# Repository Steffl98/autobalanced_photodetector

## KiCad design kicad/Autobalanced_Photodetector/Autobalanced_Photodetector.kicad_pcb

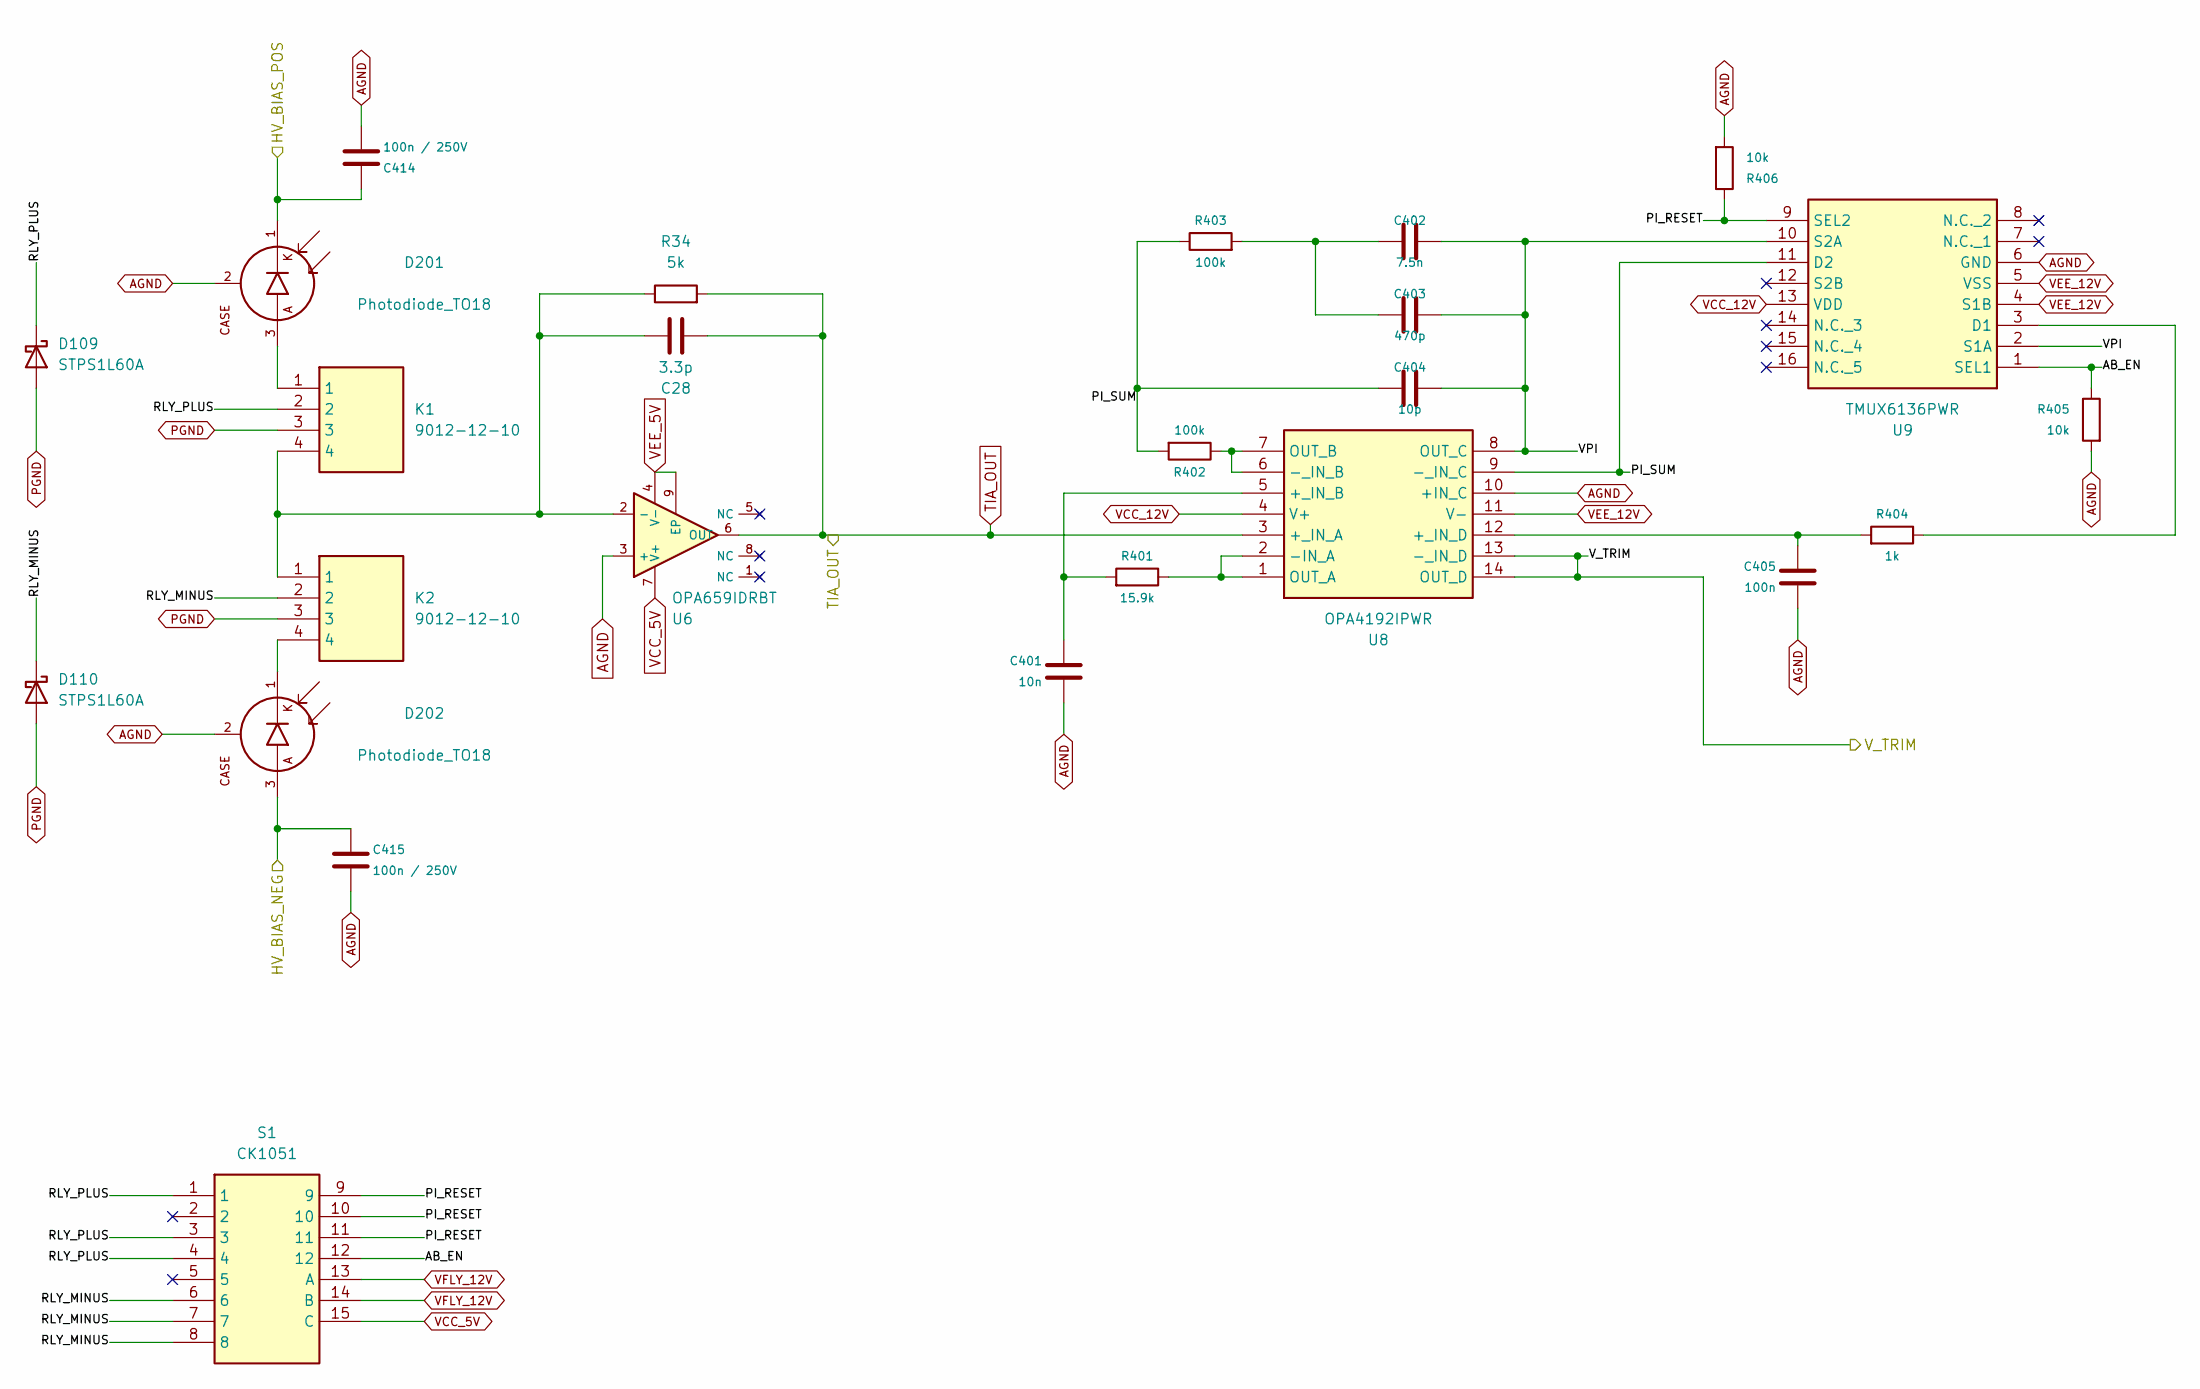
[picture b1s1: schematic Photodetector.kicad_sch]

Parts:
C28: 3.3p
C401: 10n; C_0603_1608Metric
C402: 7.5n; C_0603_1608Metric
C403: 470p; C_0603_1608Metric
C404: 10p; C_0603_1608Metric
C405: 100n; C_0603_1608Metric
C414, C415: 100n / 250V
D109, D110: STPS1L60A; D_SMA; MPN STPS1L60A
D201, D202: Photodiode_TO18; TO-18-3_Window
K1, K2: 9012-12-10; 90121210; Mouser Part Number 816-9012-12-10
R34: 5k
R401: 15.9k; R_0603_1608Metric
R402, R403: 100k; R_0603_1608Metric
R404: 1k; R_0603_1608Metric
R405, R406: 10k; R_0603_1608Metric
S1: CK1051; Manufacturer_Part_Number CK1051; Mouser Part Number 105-CK1051
U6: OPA659IDRBT; OPA659_DRB; MPN OPA659IDRBT; Mouser Part Number 595-OPA659IDRBT
U8: OPA4192IPWR; SOP65P640X120-14N; Manufacturer_Part_Number OPA4192IPWR; Mouser Part Number 595-OPA4192IPWR
U9: TMUX6136PWR; SOP65P640X120-16N; Manufacturer_Part_Number TMUX6136PWR; Mouser Part Number 595-TMUX6136PWR

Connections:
/HV_Regulator_Neg/HV_BIAS_NEG: C415.1, D202.3 (A); also elsewhere on the board
/HV_Regulator_Pos/HV_BIAS_POS: C414.1, D201.1 (K); also elsewhere on the board
/Photodetector/AB_EN: R405.1, S1.12, U9.1 (SEL1)
/Photodetector/PI_RESET: R406.1, S1.9, S1.10, S1.11, U9.9 (SEL2)
/Photodetector/PI_SUM: C404.1, R402.2, R403.1, U8.9 (-_IN_C), U9.11 (D2)
/Photodetector/RLY_MINUS: D110.1 (K), K2.2, S1.6, S1.7, S1.8
/Photodetector/RLY_PLUS: D109.1 (K), K1.2, S1.1, S1.3, S1.4
/Photodetector/VPI: C402.2, C403.2, C404.2, U8.8 (OUT_C), U9.2 (S1A), U9.10 (S2A)
/Photodetector/V_TRIM: U8.13 (-_IN_D), U8.14 (OUT_D); also elsewhere on the board
unnamed: C402.1, C403.1, R403.2
unnamed: D201.3 (A), K1.1
unnamed: D202.1 (K), K2.4
unnamed: C28.1, K1.4, K2.1, R34.1, U6.2 (-)
unnamed: C401.1, R401.2, U8.5 (+_IN_B)
unnamed: C405.1, R404.2, U8.12 (+_IN_D)
unnamed: R401.1, U8.1 (OUT_A), U8.2 (-IN_A)
unnamed: R402.1, U8.6 (-_IN_B), U8.7 (OUT_B)
unnamed: R404.1, U9.3 (D1)
PGND: D109.2 (A), D110.2 (A), K1.3, K2.3; also elsewhere on the board
TIA_OUT: C28.2, R34.2, U6.6 (OUT), U8.3 (+_IN_A)
VCC_5V: S1.15 (C), U6.7 (V+); also elsewhere on the board
VCC_12V: U8.4 (V+), U9.13 (VDD); also elsewhere on the board
VEE_5V: U6.4 (V-), U6.9 (EP); also elsewhere on the board
VEE_12V: U8.11 (V-), U9.4 (S1B), U9.5 (VSS); also elsewhere on the board
VFLY_12V: S1.13 (A), S1.14 (B); also elsewhere on the board

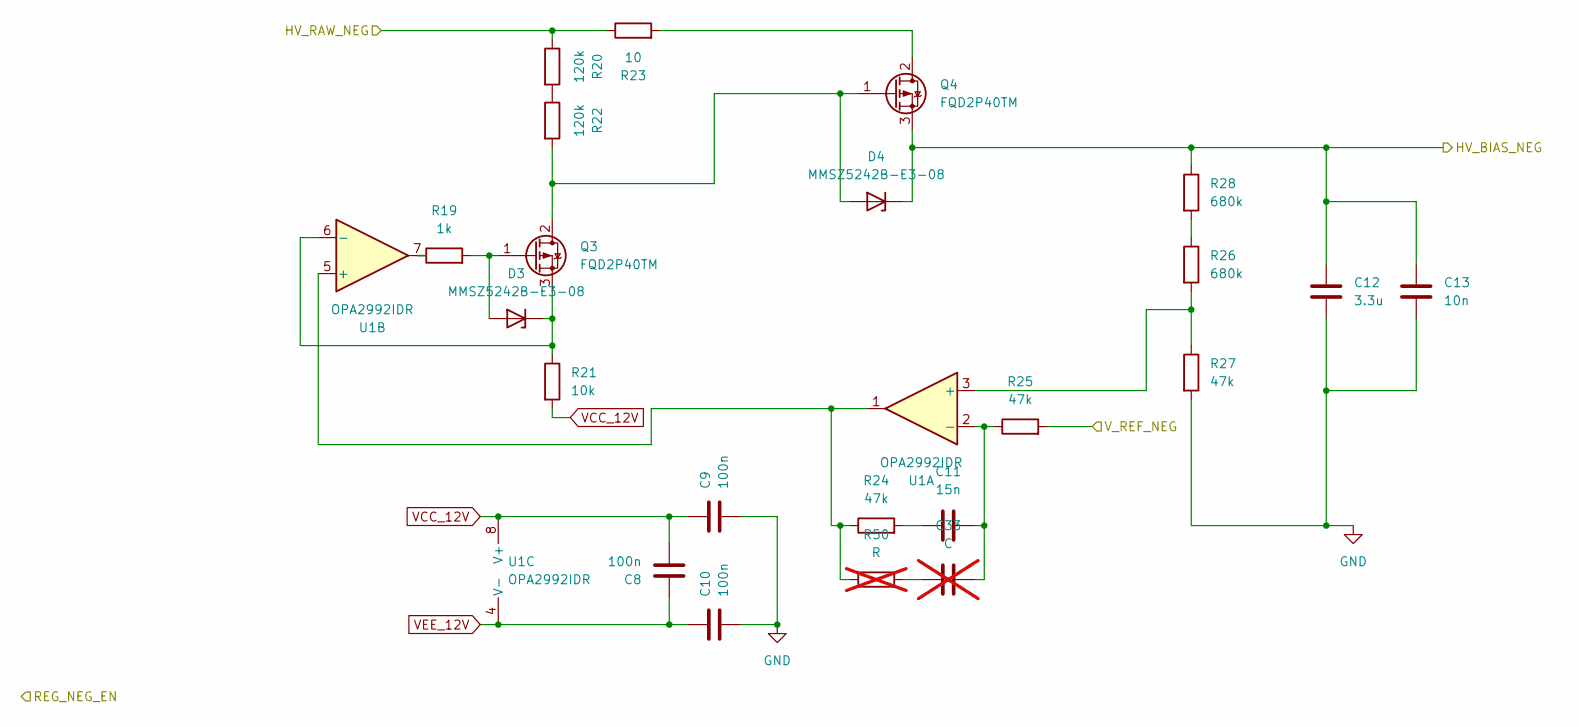
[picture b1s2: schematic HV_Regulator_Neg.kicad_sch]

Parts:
C8, C9, C10: 100n; C_0805_2012Metric; MPN C0805Y104K1RACTU
C11: 15n; C_0805_2012Metric; MPN C0805X103J5GACTU
C12: 3.3u; C_Rect_L29.0mm_W12.2mm_P27.50mm_MKT; MPN C4AQJBU4330M1WJ
C13: 10n; C_1206_3216Metric; MPN C1206C103JBGACAUTO7210
C33: C; C_0805_2012Metric; not fitted
D3, D4: MMSZ5242B-E3-08; D_SOD-123
Q3, Q4: FQD2P40TM; TO-252-2
R19: 1k; R_0805_2012Metric
R20, R22: 120k; R_1206_3216Metric
R21: 10k; R_0805_2012Metric
R23: 10; R_0805_2012Metric
R24, R25, R27: 47k; R_0805_2012Metric
R26, R28: 680k; R_1206_3216Metric
R50: R; R_0805_2012Metric; not fitted
U1: OPA2992IDR; SOIC-8_3.9x4.9mm_P1.27mm

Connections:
/Flyback/HV_RAW_NEG: R20.1, R23.1; also elsewhere on the board
/HV_Regulator_Neg/HV_BIAS_NEG: C12.1, C13.1, D4.1 (K), Q4.3 (S), R28.1; also elsewhere on the board
/HV_Regulator_Neg/V_REF_NEG: R25.2; also elsewhere on the board
unnamed: C11.1, R24.2
unnamed: C33.1, R50.2
unnamed: D3.2 (A), Q3.1 (G), R19.2
unnamed: D3.1 (K), Q3.3 (S), R21.1, U1.6 (-)
unnamed: D4.2 (A), Q3.2 (D), Q4.1 (G), R22.2
unnamed: Q4.2 (D), R23.2
unnamed: R19.1, U1.7
unnamed: R20.2, R22.1
unnamed: R26.1, R28.2
unnamed: R26.2, R27.1, U1.3 (+)
unnamed: C11.2, C33.2, R25.1, U1.2 (-)
unnamed: R24.1, R50.1, U1.1, U1.5 (+)
VCC_12V: C8.2, C9.1, R21.2, U1.8 (V+); also elsewhere on the board
VEE_12V: C8.1, C10.1, U1.4 (V-); also elsewhere on the board

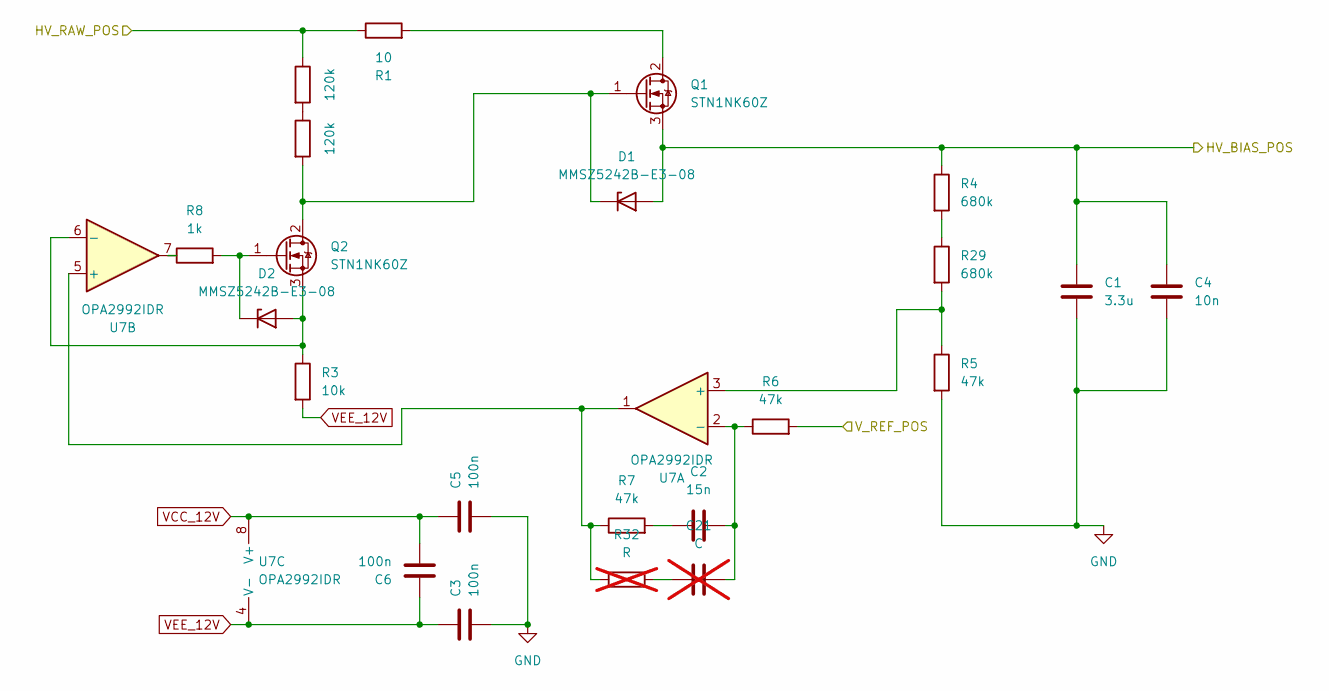
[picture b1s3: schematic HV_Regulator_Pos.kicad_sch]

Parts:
C1: 3.3u; C_Rect_L29.0mm_W12.2mm_P27.50mm_MKT; MPN C4AQJBU4330M1WJ
C2: 15n; C_0805_2012Metric; MPN C0805X103J5GACTU
C3, C5, C6: 100n; C_0805_2012Metric; MPN C0805Y104K1RACTU
C4: 10n; C_1206_3216Metric; MPN C1206C103JBGACAUTO7210
C21: C; C_0805_2012Metric; not fitted
D1, D2: MMSZ5242B-E3-08; D_SOD-123
Q1, Q2: STN1NK60Z; SOT-223
R1: 10; R_0805_2012Metric
R2, R9: 120k; R_1206_3216Metric
R3: 10k; R_0805_2012Metric
R4, R29: 680k; R_1206_3216Metric
R5, R6, R7: 47k; R_0805_2012Metric
R8: 1k; R_0805_2012Metric
R32: R; R_0805_2012Metric; not fitted
U7: OPA2992IDR; SOIC-8_3.9x4.9mm_P1.27mm

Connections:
/Flyback/HV_RAW_POS: R1.1, R9.1; also elsewhere on the board
/HV_Regulator_Pos/HV_BIAS_POS: C1.1, C4.1, D1.2 (A), Q1.3 (S), R4.1; also elsewhere on the board
/HV_Regulator_Pos/V_REF_POS: R6.2; also elsewhere on the board
unnamed: C2.1, R7.2
unnamed: C21.1, R32.2
unnamed: D1.1 (K), Q1.1 (G), Q2.2 (D), R2.2
unnamed: D2.2 (A), Q2.3 (S), R3.1, U7.6 (-)
unnamed: D2.1 (K), Q2.1 (G), R8.2
unnamed: Q1.2 (D), R1.2
unnamed: R2.1, R9.2
unnamed: R8.1, U7.7
unnamed: R4.2, R29.1
unnamed: R5.1, R29.2, U7.3 (+)
unnamed: C2.2, C21.2, R6.1, U7.2 (-)
unnamed: R7.1, R32.1, U7.1, U7.5 (+)
VCC_12V: C5.1, C6.2, U7.8 (V+); also elsewhere on the board
VEE_12V: C3.1, C6.1, R3.2, U7.4 (V-); also elsewhere on the board

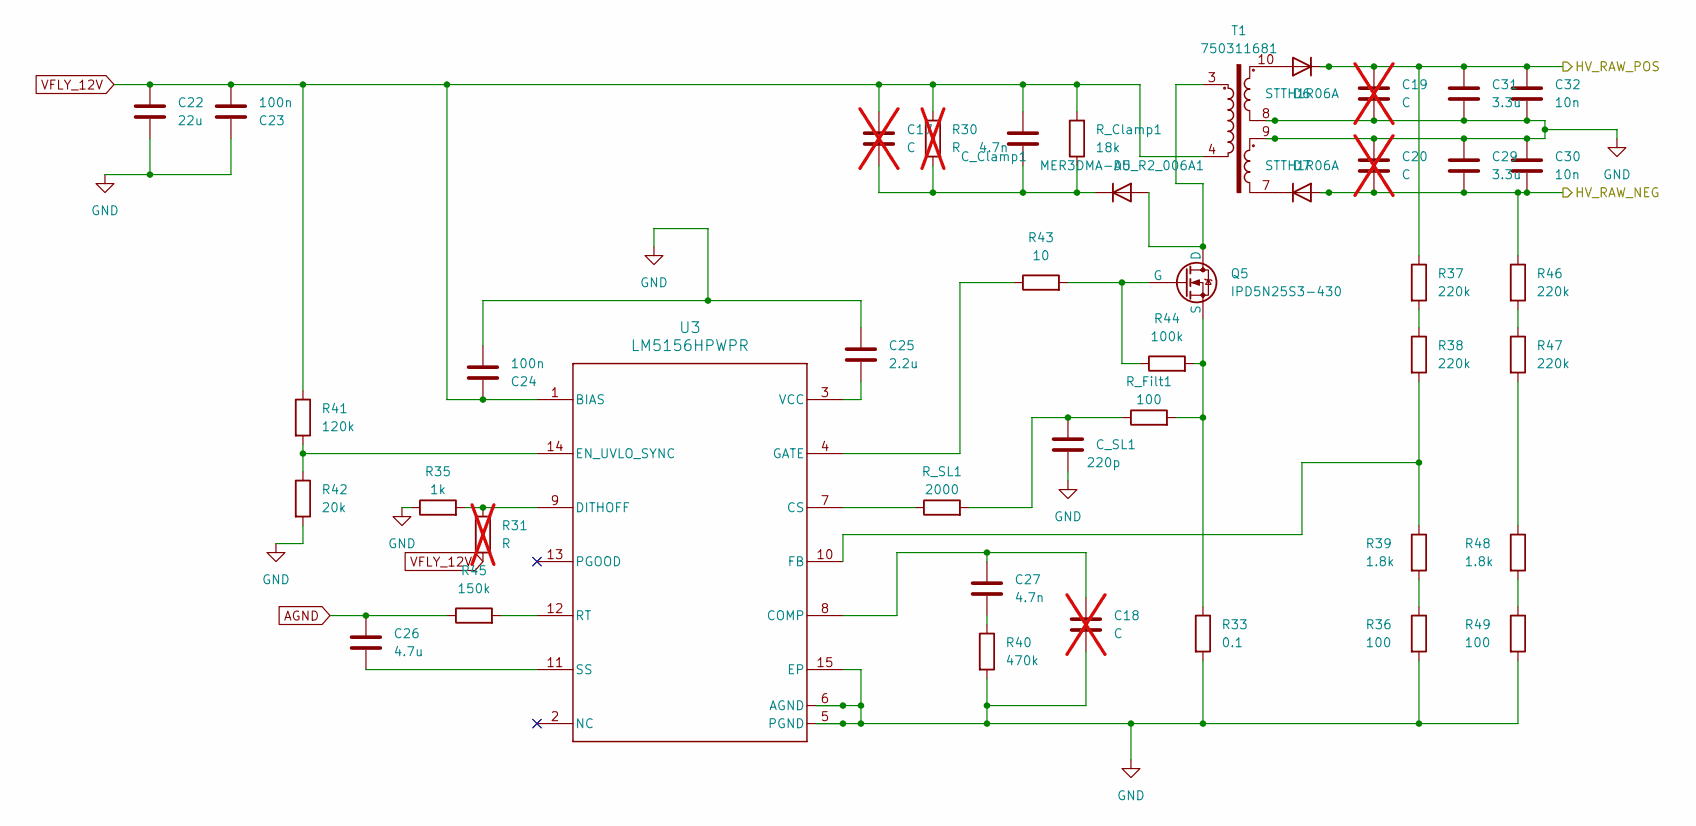
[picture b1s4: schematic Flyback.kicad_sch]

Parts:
C17, C18, C19, C20: C; C_0805_2012Metric; not fitted
C22: 22u; C_1210_3225Metric; MPN C3225X7R1E226M250AB
C23, C24: 100n; C_0805_2012Metric; MPN C0805Y104K1RACTU
C25: 2.2u; C_0805_2012Metric; MPN GRM21BR71C225KA12L
C26: 4.7u; C_0805_2012Metric; MPN CL21A475KAQNNNG
C27: 4.7n; C_0805_2012Metric; MPN GRM2165C1H472JA01D
C29, C31: 3.3u; C_Rect_L29.0mm_W12.2mm_P27.50mm_MKT; MPN C4AQJBU4330M1WJ
C30, C32: 10n; C_1206_3216Metric; MPN C1206C103JBGACAUTO7210
C_Clamp1: 4.7n; C_1206_3216Metric; MPN C1206C472JBGACTU
C_SL1: 220p; C_0805_2012Metric; MPN C0G
D5: MER3DMA-AU_R2_006A1; D_SMA
D6, D7: STTH1R06A; D_SMA
Q5: IPD5N25S3-430; TO-252-2
R30, R31: R; R_0805_2012Metric; not fitted
R33: 0.1; R_0805_2012Metric
R35: 1k; R_0805_2012Metric
R36, R49: 100; R_0805_2012Metric
R37, R38, R46, R47: 220k; R_1206_3216Metric
R39, R48: 1.8k; R_0805_2012Metric
R40: 470k; R_0805_2012Metric
R41: 120k; R_0805_2012Metric
R42: 20k; R_0805_2012Metric
R43: 10; R_0805_2012Metric
R44: 100k; R_0805_2012Metric
R45: 150k; R_0805_2012Metric
R_Clamp1: 18k; R_0805_2012Metric
R_Filt1: 100; R_0805_2012Metric
R_SL1: 2000; R_0805_2012Metric
T1: 750311681; Wuerth_750311681
U3: LM5156HPWPR; PWP0014H-IPC_A

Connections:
/Flyback/HV_RAW_NEG: C20.2, C29.2, C30.2, D7.2 (A), R46.1; also elsewhere on the board
/Flyback/HV_RAW_POS: C19.1, C31.1, C32.1, D6.1 (K), R37.1; also elsewhere on the board
unnamed: C27.1, R40.1
unnamed: C_SL1.2, R_Filt1.1, R_SL1.2
unnamed 37: D5.2 (A), Q5.1 (D), T1.3; also elsewhere on the board
unnamed: C17.2, C_Clamp1.2, D5.1 (K), R30.2, R_Clamp1.1
unnamed 39: D6.2 (A), T1.10; also elsewhere on the board
unnamed 40: D7.1 (K), T1.7; also elsewhere on the board
unnamed: Q5.2 (G), R43.2, R44.1
unnamed: Q5.3 (S), R33.1, R44.2, R_Filt1.2
unnamed: R36.1, R39.2
unnamed: R37.2, R38.1
unnamed: R46.2, R47.1
unnamed: R47.2, R48.1
unnamed: R48.2, R49.1
unnamed: C18.1, C27.2, U3.8 (COMP)
unnamed: R_SL1.1, U3.7 (CS)
unnamed: R31.1, R35.2, U3.9 (DITHOFF)
unnamed: R41.2, R42.1, U3.14 (EN_UVLO_SYNC)
unnamed: R38.2, R39.1, U3.10 (FB)
unnamed: R43.1, U3.4 (GATE)
unnamed: R45.2, U3.12 (RT)
unnamed: C26.2, U3.11 (SS)
unnamed: C25.2, U3.3 (VCC)
VFLY_12V: C17.1, C22.1, C23.2, C24.1, C_Clamp1.1, R30.1, R31.2, R41.1, R_Clamp1.2, T1.4, U3.1 (BIAS); also elsewhere on the board

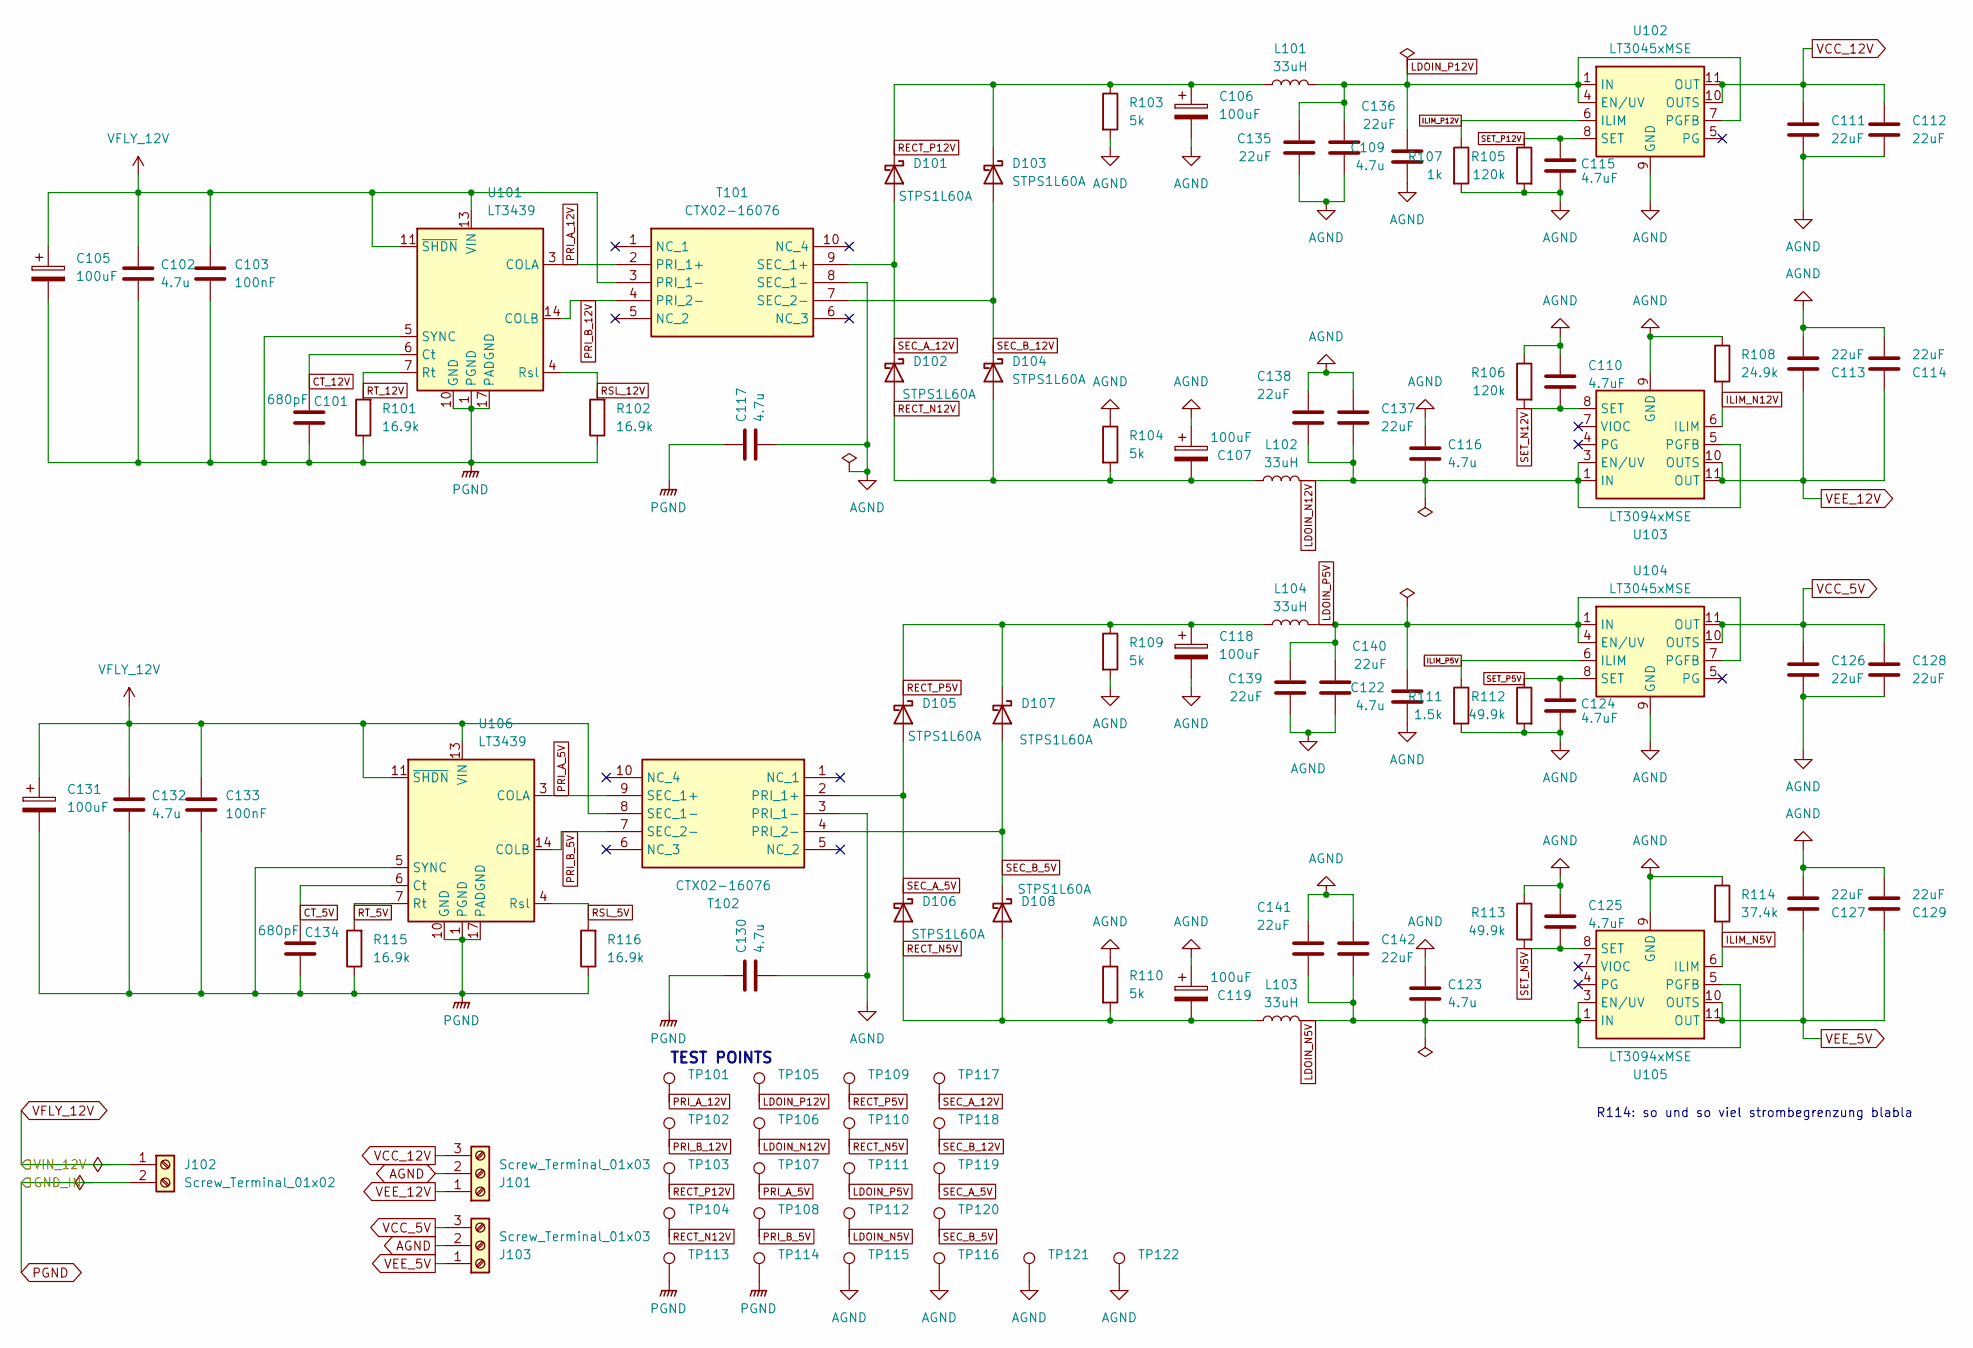
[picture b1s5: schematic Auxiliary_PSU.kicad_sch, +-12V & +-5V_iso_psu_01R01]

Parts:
C101, C134: 680pF; C_0603_1608Metric; MPN CC0603FRNPO9BN681
C102, C109, C116, C117, C122, C123, C130, C132: 4.7u; C_1206_3216Metric; MPN KGM31AR71E475KU
C103, C133: 100nF; C_0603_1608Metric; MPN CGA3E2X7R1E104M080AA
C105, C106, C107, C118, C119, C131: 100uF; CP_Elec_6.3x7.7; MPN GYE1V101MCQ1GS
C110, C115, C124, C125: 4.7uF; C_0603_1608Metric; MPN C1608X5R1E475K080AC
C111, C112, C113, C114, C126, C127, C128, C129, C135, C136, C137, C138, C139, C140, C141, C142: 22uF; C_1210_3225Metric; MPN MAAST32MSB7226MPNA01
D101, D102, D103, D104, D105, D106, D107, D108: STPS1L60A; D_SMA; MPN STPS1L60A
J101, J103: Screw_Terminal_01x03; TerminalBlock_Phoenix_MKDS-1,5-3-5.08_1x03_P5.08mm_Horizont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; MPN 1715734
J102: Screw_Terminal_01x02; TerminalBlock_Phoenix_MKDS-1,5-2-5.08_1x02_P5.08mm_Horizont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; MPN 1715721
L101, L102, L103, L104: 33uH; L_TDK_VLS5030EX
R101, R102, R115, R116: 16.9k; R_0603_1608Metric; MPN CPF0603F16K9C1
R103, R104, R109, R110: 5k; R_1206_3216Metric; MPN RT0603BRE075KL
R105, R106: 120k; R_0603_1608Metric; MPN RT0603BRD07120KL
R107: 1k; R_0603_1608Metric; MPN RT0603BRD071KL
R108: 24.9k; R_0603_1608Metric; MPN RT0603BRD0724K9L
R111: 1.5k; R_0603_1608Metric; MPN RT0603BRD071K5L
R112, R113: 49.9k; R_0603_1608Metric; MPN RT0603BRD0749K9L
R114: 37.4k; R_0603_1608Metric; MPN RT0603BRE0737K4L
T101, T102: CTX02-16076; CTX0216076; Mouser Part Number 704-CTX02-16076
TP101: PRI_A_12V; TestPoint_Pad_D1.5mm
TP102: PRI_B_12V; TestPoint_Pad_D1.5mm
TP103: RECT_P12V; TestPoint_Pad_D1.5mm
TP104: RECT_N12V; TestPoint_Pad_D1.5mm
TP105: LDOIN_P12V; TestPoint_Pad_D1.5mm
TP106: LDOIN_N12V; TestPoint_Pad_D1.5mm
TP107: PRI_A_5V; TestPoint_Pad_D1.5mm
TP108: PRI_B_5V; TestPoint_Pad_D1.5mm
TP109: RECT_P5V; TestPoint_Pad_D1.5mm
TP110: RECT_N5V; TestPoint_Pad_D1.5mm
TP111: LDOIN_P5V; TestPoint_Pad_D1.5mm
TP112: LDOIN_N5V; TestPoint_Pad_D1.5mm
TP113, TP114: PGND; TestPoint_Keystone_5000-5004_Miniature; MPN 5001
TP115, TP116, TP121, TP122: AGND; TestPoint_Keystone_5000-5004_Miniature; MPN 5001
TP117: SEC_A_12V; TestPoint_Pad_D1.5mm
TP118: SEC_B_12V; TestPoint_Pad_D1.5mm
TP119: SEC_A_5V; TestPoint_Pad_D1.5mm
TP120: SEC_B_5V; TestPoint_Pad_D1.5mm
U101, U106: LT3439; TSSOP-16-1EP_4.4x5mm_P0.65mm
U102, U104: LT3045xMSE; MSOP-12-1EP_3x4.039mm_P0.65mm_EP1.651x2.845mm; MPN LT3045HMSE#TRPBF
U103, U105: LT3094xMSE; MSOP-12-1EP_3x4.039mm_P0.65mm_EP1.651x2.845mm; MPN LT3094EMSE#TRPBF

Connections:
CT_5V: C134.1, U106.6 (Ct)
CT_12V: C101.1, U101.6 (Ct)
ILIM_N5V: R114.2, U105.6 (ILIM)
ILIM_N12V: R108.2, U103.6 (ILIM)
ILIM_P5V: R111.1, U104.6 (ILIM)
ILIM_P12V: R107.1, U102.6 (ILIM)
LDOIN_N5V: C123.2, C141.2, C142.2, L103.2, TP112.1, U105.1 (IN), U105.2 (IN), U105.3 (EN/UV), U105.5 (PGFB), U105.13 (IN)
LDOIN_N12V: C116.2, C137.2, C138.2, L102.2, TP106.1, U103.1 (IN), U103.2 (IN), U103.3 (EN/UV), U103.5 (PGFB), U103.13 (IN)
LDOIN_P5V: C122.1, C139.1, C140.1, L104.2, TP111.1, U104.1 (IN), U104.2 (IN), U104.3 (IN), U104.4 (EN/UV), U104.7 (PGFB)
LDOIN_P12V: C109.1, C135.1, C136.1, L101.2, TP105.1, U102.1 (IN), U102.2 (IN), U102.3 (IN), U102.4 (EN/UV), U102.7 (PGFB)
PGND: C101.2, C102.2, C103.2, C105.2, C117.1, C130.1, C131.2, C132.2, C133.2, C134.2, J102.2, R101.1, R102.1, R115.1, R116.1, TP113.1, TP114.1, U101.1 (PGND), U101.5 (SYNC), U101.10 (GND), U101.16 (PGND), U101.17 (PADGND), U106.1 (PGND), U106.5 (SYNC), U106.10 (GND), U106.16 (PGND), U106.17 (PADGND); also elsewhere on the board
PRI_A_5V: T102.9 (SEC_1+), TP107.1, U106.3 (COLA)
PRI_A_12V: T101.2 (PRI_1+), TP101.1, U101.3 (COLA)
PRI_B_5V: T102.7 (SEC_2-), TP108.1, U106.14 (COLB)
PRI_B_12V: T101.4 (PRI_2-), TP102.1, U101.14 (COLB)
RECT_N5V: C119.2, D106.2 (A), D108.2 (A), L103.1, R110.2, TP110.1
RECT_N12V: C107.2, D102.2 (A), D104.2 (A), L102.1, R104.2, TP104.1
RECT_P5V: C118.1, D105.1 (K), D107.1 (K), L104.1, R109.1, TP109.1
RECT_P12V: C106.1, D101.1 (K), D103.1 (K), L101.1, R103.1, TP103.1
RSL_5V: R116.2, U106.4 (Rsl)
RSL_12V: R102.2, U101.4 (Rsl)
RT_5V: R115.2, U106.7 (Rt)
RT_12V: R101.2, U101.7 (Rt)
SEC_A_5V: D105.2 (A), D106.1 (K), T102.2 (PRI_1+), TP119.1
SEC_A_12V: D101.2 (A), D102.1 (K), T101.9 (SEC_1+), TP117.1
SEC_B_5V: D107.2 (A), D108.1 (K), T102.4 (PRI_2-), TP120.1
SEC_B_12V: D103.2 (A), D104.1 (K), T101.7 (SEC_2-), TP118.1
SET_N5V: C125.2, R113.2, U105.8 (SET)
SET_N12V: C110.2, R106.2, U103.8 (SET)
SET_P5V: C124.1, R112.1, U104.8 (SET)
SET_P12V: C115.1, R105.1, U102.8 (SET)
VCC_5V: C126.1, C128.1, J103.3, U104.10 (OUTS), U104.11 (OUT), U104.12 (OUT); also elsewhere on the board
VCC_12V: C111.1, C112.1, J101.3, U102.10 (OUTS), U102.11 (OUT), U102.12 (OUT); also elsewhere on the board
VEE_5V: C127.1, C129.1, J103.1, U105.10 (OUTS), U105.11 (OUT), U105.12 (OUT); also elsewhere on the board
VEE_12V: C113.1, C114.1, J101.1, U103.10 (OUTS), U103.11 (OUT), U103.12 (OUT); also elsewhere on the board
VFLY_12V: C102.1, C103.1, C105.1, C131.1, C132.1, C133.1, J102.1, T101.3 (PRI_1-), T102.8 (SEC_1-), U101.11 (~SHDN), U101.13 (VIN), U106.11 (~SHDN), U106.13 (VIN); also elsewhere on the board

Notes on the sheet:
R114: so und so viel strombegrenzung blabla
TEST POINTS

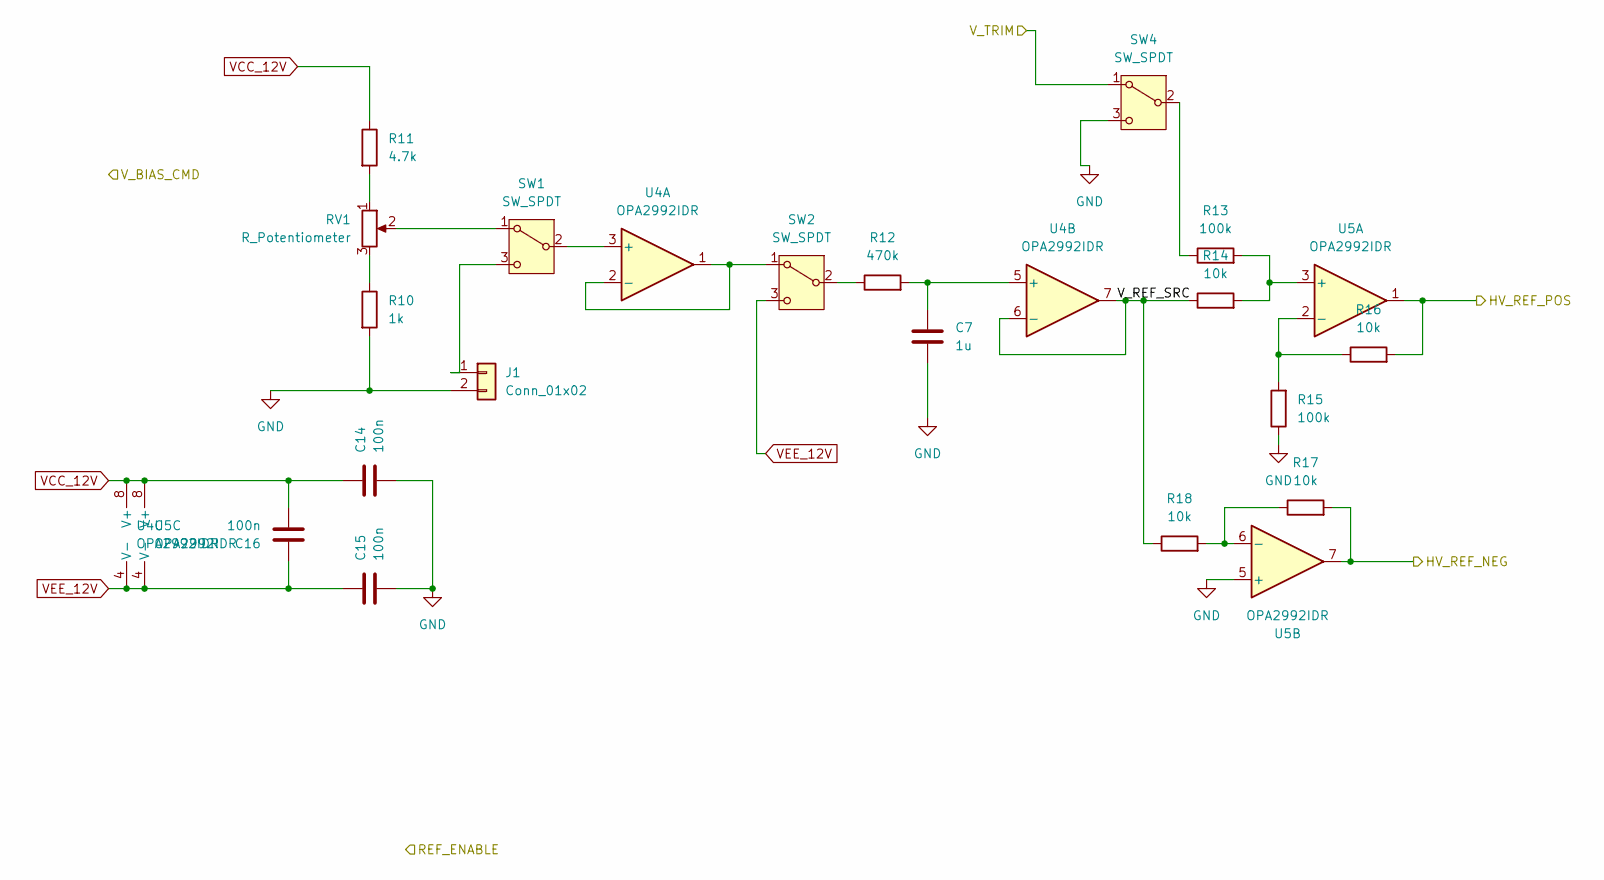
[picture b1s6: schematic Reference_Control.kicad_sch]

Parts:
C7: 1u; C_Rect_L13.0mm_W4.0mm_P10.00mm_FKS3_FKP3_MKS4; MPN MKS4C041003C00KSSD
C14, C15, C16: 100n; C_0805_2012Metric; MPN C0805Y104K1RACTU
J1: Conn_01x02; TerminalBlock_Phoenix_MKDS-1,5-2-5.08_1x02_P5.08mm_Horizont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; MPN 1715721
R10: 1k; R_0805_2012Metric
R11: 4.7k; R_0805_2012Metric
R12: 470k; R_0805_2012Metric
R13, R15: 100k; R_0805_2012Metric
R14, R16, R17, R18: 10k; R_0805_2012Metric
RV1: R_Potentiometer; Potentiometer_Bourns_PTV09A-1_Single_Vertical
SW1, SW2, SW4: SW_SPDT; SW_Slide_SPDT_Straight_CK_OS102011MS2Q; MPN OS102011MS2QN1
U4, U5: OPA2992IDR; SOIC-8_3.9x4.9mm_P1.27mm

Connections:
/HV_Regulator_Neg/V_REF_NEG: R17.2, U5.7; also elsewhere on the board
/HV_Regulator_Pos/V_REF_POS: R16.2, U5.1; also elsewhere on the board
/Photodetector/V_TRIM: SW4.1 (A); also elsewhere on the board
/Reference_Control/V_REF_SRC: R14.1, R18.1, U4.6 (-), U4.7
unnamed: J1.1, SW1.3 (C)
unnamed: R10.1, RV1.3
unnamed: R11.2, RV1.1
unnamed: RV1.2, SW1.1 (A)
unnamed: SW1.2 (B), U4.3 (+)
unnamed: SW2.1 (A), U4.1, U4.2 (-)
unnamed: R12.1, SW2.2 (B)
unnamed: R13.1, SW4.2 (B)
unnamed: C7.1, R12.2, U4.5 (+)
unnamed: R13.2, R14.2, U5.3 (+)
unnamed: R15.2, R16.1, U5.2 (-)
unnamed: R17.1, R18.2, U5.6 (-)
VCC_12V: C14.1, C16.2, R11.1, U4.8 (V+), U5.8 (V+); also elsewhere on the board
VEE_12V: C15.1, C16.1, SW2.3 (C), U4.4 (V-), U5.4 (V-); also elsewhere on the board

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
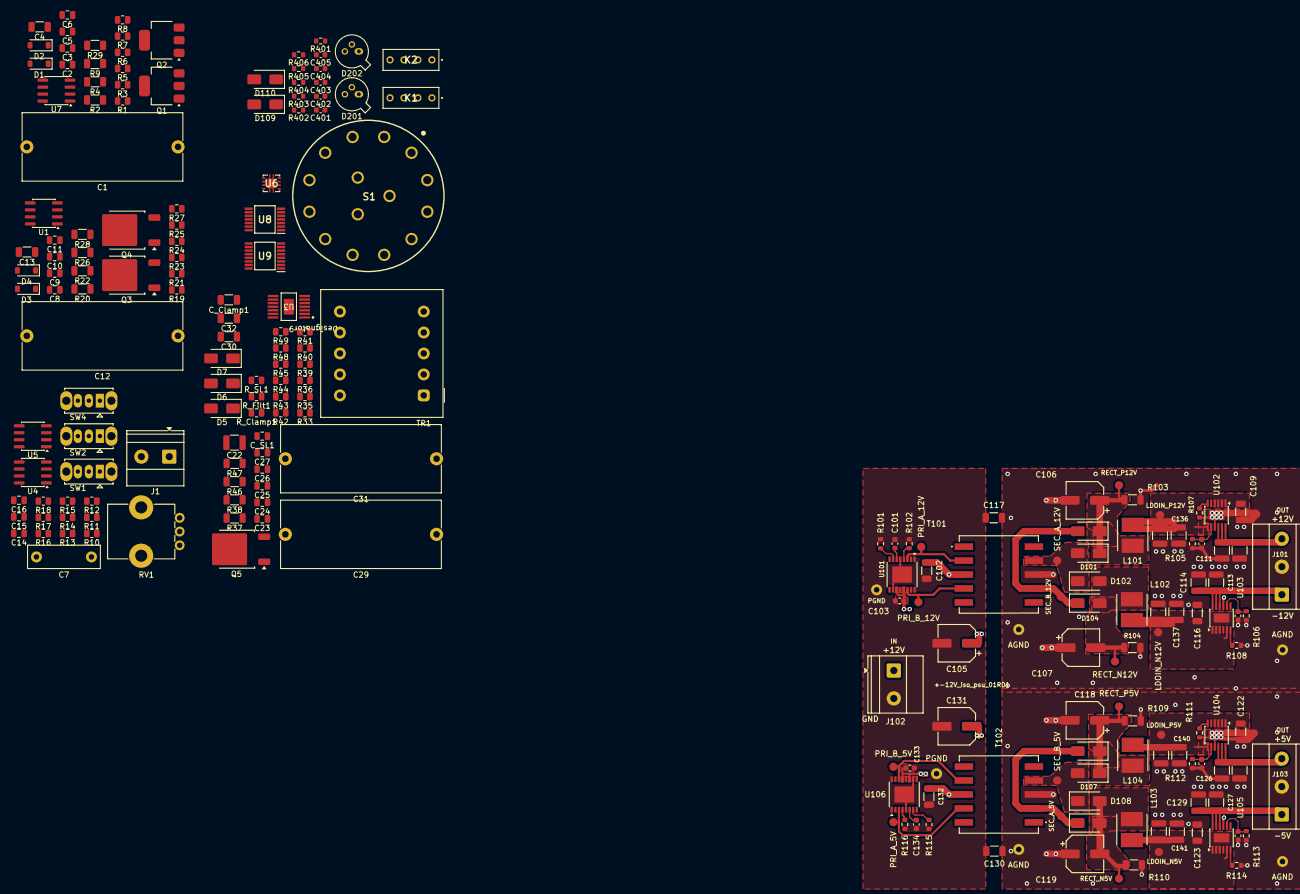
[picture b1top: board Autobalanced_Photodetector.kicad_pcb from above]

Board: 2 copper layers, 219 parts (0 on the bottom side), 117 nets.

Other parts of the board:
TR1: Wuerth 750311681C enter-Tapped; Transformer_Wuerth_750343373

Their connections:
unnamed 37: TR1.1; also elsewhere on the board
unnamed 39: TR1.4; also elsewhere on the board
unnamed 40: TR1.6; also elsewhere on the board
VFLY_12V: TR1.3; also elsewhere on the board
